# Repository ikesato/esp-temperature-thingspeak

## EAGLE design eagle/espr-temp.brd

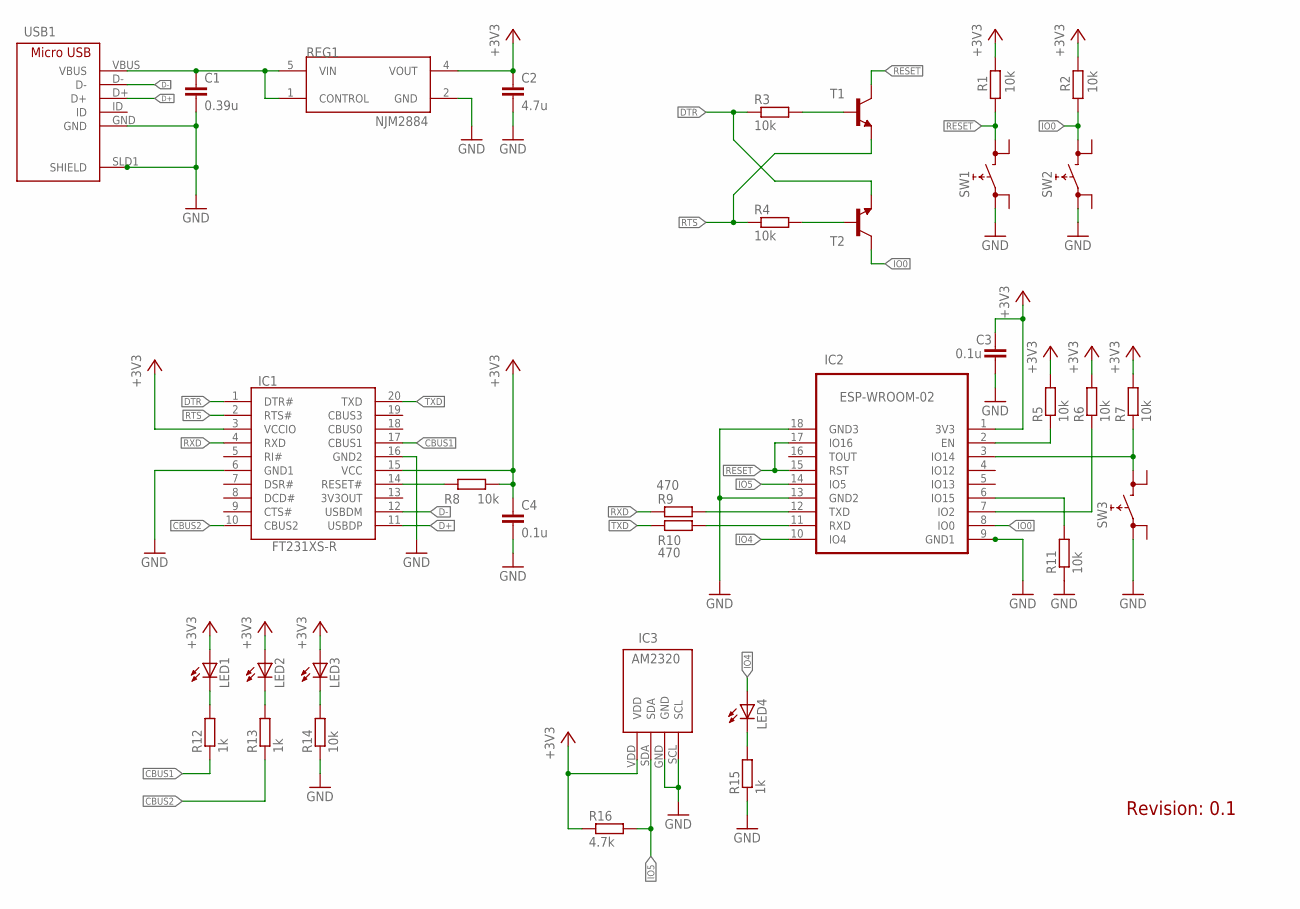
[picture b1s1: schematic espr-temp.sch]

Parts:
C1: 0.39u; C1608
C2: 4.7u; C3216
C3, C4: 0.1u; C2012
IC1: FT231XS-R; SOP64P599X175-20N
IC2: ESP-WROOM-02
IC3: AM2320
LED1: OSHR1608; C1608
LED2: OSYG1608; C1608
LED3: OSYL1608; C1608
LED4: OSBL1608; C1608
R1, R2, R3, R4, R5, R6, R7, R8, R11, R14: 10k; R1608
R9, R10: 470; R1608
R12, R13, R15: 1k; R1608
R16: 4.7k; M0805
REG1: NJM2884; NJM2884-SOT-89-5
SW1, SW2, SW3: SKRPACE010
T1, T2: 2PD601A; SOT346
USB1: MICRO-USB; ZX62B5PA

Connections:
+3V3: C2.1, C3.1, C4.1, IC1.3 (VCCIO), IC1.15 (VCC), IC2.1 (3V3), IC3.VDD, LED1.A, LED2.A, LED3.A, R1.2, R2.2, R5.2, R6.2, R7.2, R8.2, R16.1, REG1.4 (VOUT)
CBUS1: IC1.17 (CBUS1), R12.1
CBUS2: IC1.10 (CBUS2), R13.1
D+: IC1.11 (USBDP), USB1.D+
D-: IC1.12 (USBDM), USB1.D-
DTR: IC1.1 (DTR#), R3.1, T2.2 (E)
GND: C1.2, C2.2, C3.2, C4.2, IC1.6 (GND1), IC1.16 (GND2), IC2.9 (GND1), IC2.13 (GND2), IC2.18 (GND3), IC2.19 (GND0), IC3.GND, IC3.SCL, R11.1, R14.1, R15.1, REG1.2 (GND), SW1.1 (0), SW2.1 (0), SW3.1 (0), USB1.GND, USB1.SLD1 (SHIELD), USB1.SLD2 (SHIELD2), USB1.SLD3 (SHIELD3), USB1.SLD4 (SHIELD4), USB1.SLD5 (SHIELD5), USB1.SLD6 (SHIELD6)
IO0: IC2.8 (IO0), R2.1, SW2.3 (1), T2.3 (C)
IO4: IC2.10 (IO4), LED4.A
IO5: IC2.14 (IO5), IC3.SDA, R16.2
unnamed: IC2.2 (EN), R5.1
unnamed: LED4.C, R15.2
unnamed: IC2.7 (IO2), R6.1
unnamed: C1.1, REG1.1 (CONTROL), REG1.5 (VIN), USB1.VBUS
unnamed: LED1.C, R12.2
unnamed: R3.2, T1.1 (B)
unnamed: R4.2, T2.1 (B)
unnamed: LED2.C, R13.2
unnamed: LED3.C, R14.2
unnamed: IC2.12 (TXD), R9.2
unnamed: IC2.11 (RXD), R10.2
unnamed: IC2.6 (IO15), R11.2
unnamed: IC1.14 (RESET#), R8.1
unnamed: IC2.3 (IO14), R7.1, SW3.3 (1)
RESET: IC2.15 (RST), IC2.17 (IO16), R1.1, SW1.3 (1), T1.3 (C)
RTS: IC1.2 (RTS#), R4.1, T1.2 (E)
RXD: IC1.4 (RXD), R9.1
TXD: IC1.20 (TXD), R10.1

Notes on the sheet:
Revision: 0.1

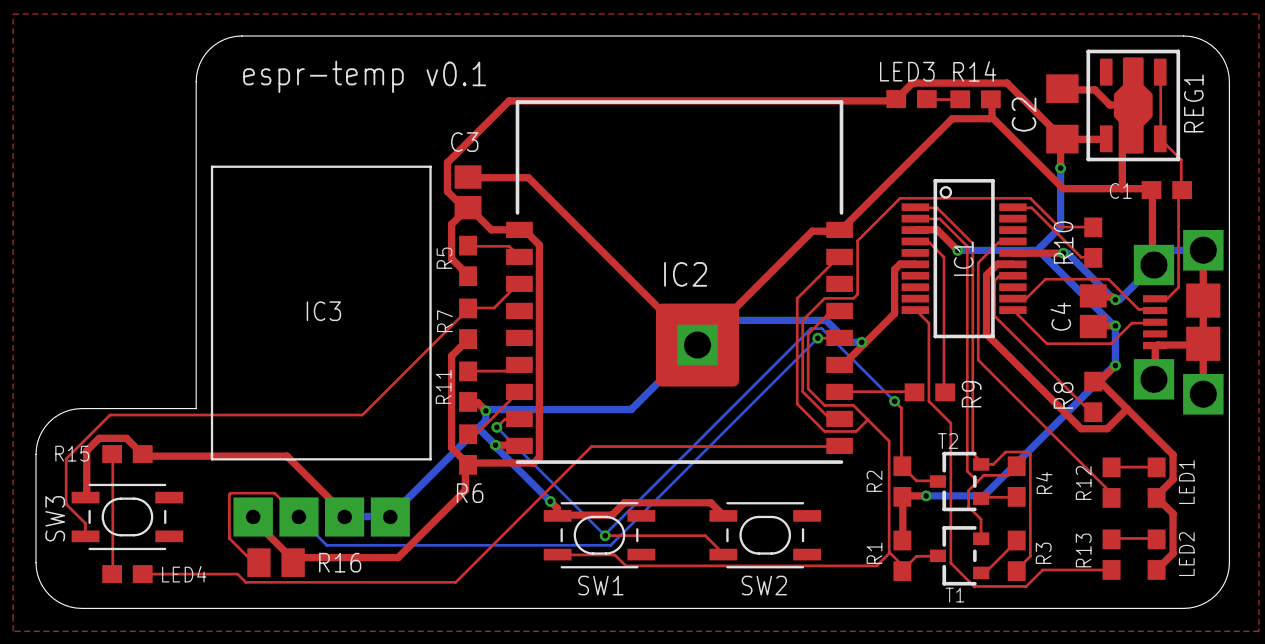
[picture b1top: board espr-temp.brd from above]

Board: 2 copper layers, 66.3 x 31.8 mm, 34 parts (0 on the bottom side), 28 nets.

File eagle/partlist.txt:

Partlist

Exported from espr-temp.sch at 2018/05/29 20:20

EAGLE Version 8.3.1 Copyright (c) 1988-2017 Autodesk, Inc.

Assembly variant: 

Part     Value          Device                 Package           Library       Sheet   value? akituki? have?

C1       0.39u          C-EUC1608              C1608             rcl           1       x      x        仙石で買う
C2       4.7u           C-EUC3216              C3216             rcl           1       x      x        x
C3       0.1u           C-EUC2012              C2012             rcl           1       x      x        x
C4       0.1u           C-EUC2012              C2012             rcl           1       x      x        x
IC1      FT231XS-R      FT231XS-R              SOP64P599X175-20N FT231XS-R     1       x      x        x
IC2      ESP-WROOM-02   ESP-WROOM-02FRONT-FACE FRONT-FACE        esp-wroom-02  1       x      x        x
IC3      AM2320         AM2320                 AM2320            am2320        1       x      x        x
LED1     (RX red)       OSHR1608               C1608             led-smd       1       x      x        秋月で買う
LED2     (TX green)     OSYG1608               C1608             led-smd       1       x      x        x
LED3     (prw yellow)   OSYL1608               C1608             led-smd       1       x      x        x
LED4     (apl blue)     OSBL1608               C1608             led-smd       1       x      x        秋月で買う
R1       10k            R1608                  R1608             registors     1       x      x        仙石0.1w 1608 を買う
R2       10k            R1608                  R1608             registors     1       x      x        仙石0.1w 1608 を買う
R3       10k            R1608                  R1608             registors     1       x      x        仙石0.1w 1608 を買う
R4       10k            R1608                  R1608             registors     1       x      x        仙石0.1w 1608 を買う
R5       10k            R1608                  R1608             registors     1       x      x        仙石0.1w 1608 を買う
R6       10k            R1608                  R1608             registors     1       x      x        仙石0.1w 1608 を買う
R7       10k            R1608                  R1608             registors     1       x      x        仙石0.1w 1608 を買う
R8       10k            R1608                  R1608             registors     1       x      x        仙石0.1w 1608 を買う
R9       470            R1608                  R1608             registors     1       x      x        仙石0.1w 1608 を買う
R10      470            R1608                  R1608             registors     1       x      x        仙石0.1w 1608 を買う
R11      10k            R1608                  R1608             registors     1       x      x        仙石0.1w 1608 を買う
R12      1k             R1608                  R1608             registors     1       x      x        仙石0.1w 1608 を買う
R13      1k             R1608                  R1608             registors     1       x      x        仙石0.1w 1608 を買う
R14      10k            R1608                  R1608             registors     1       x      x        仙石0.1w 1608 を買う
R15      1k             R1608                  R1608             registors     1       x      x        仙石0.1w 1608 を買う
R16      4.7k           R-EU_M0805             M0805             rcl           1       x      x        x TODO:ほんとに持ってる？
REG1     NJM2884U1      NJM2884U1              SOT-89-5          regulator     1       x      x        秋月で買う
SW1                     SKRPACE010             SKRPACE010        switches      1       x      x        x
SW2                     SKRPACE010             SKRPACE010        switches      1       x      x        x
SW3                     SKRPACE010             SKRPACE010        switches      1       x      x        x
T1                      2PD601A                SOT346            transistors   1       x      x        秋月で買う
T2                      2PD601A                SOT346            transistors   1       x      x        秋月で買う
USB1     MICRO-USB      MICRO-USB              ZX62B5PA          usb-connector 1       x      x        x

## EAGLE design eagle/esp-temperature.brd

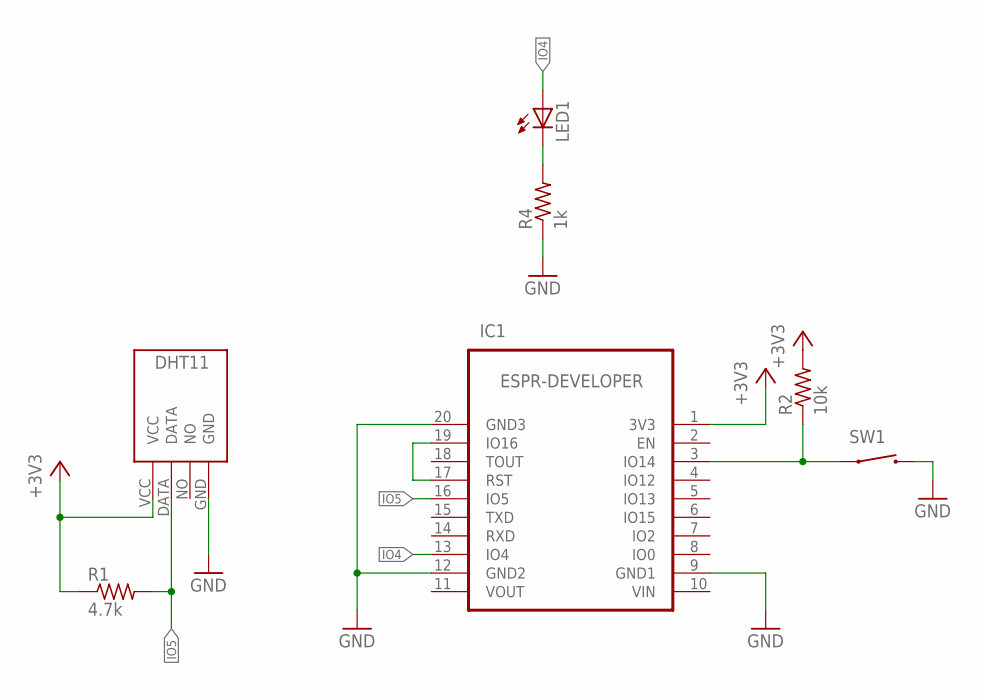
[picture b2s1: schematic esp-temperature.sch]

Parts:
IC1: ESPR-DEVELOPER
LED1: LED-SIDEUP2; LED5MM-SIDE-UP2
R1: 4.7k; R0805
R2: 10k; R0805
R4: 1k; R0805
SW1: TVBP06
U$1: DHT11

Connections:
+3V3: IC1.1 (3V3), R1.1, R2.2, U$1.VCC
GND: IC1.9 (GND1), IC1.12 (GND2), IC1.20 (GND3), R4.1, SW1.2, U$1.GND
IO4: IC1.13 (IO4), LED1.A
IO5: IC1.16 (IO5), R1.2, U$1.DATA
unnamed: IC1.3 (IO14), R2.1, SW1.1
unnamed: LED1.K (C), R4.2
unnamed: IC1.17 (RST), IC1.19 (IO16)
VIN: IC1.10 (VIN)
VOUT: IC1.11 (VOUT)

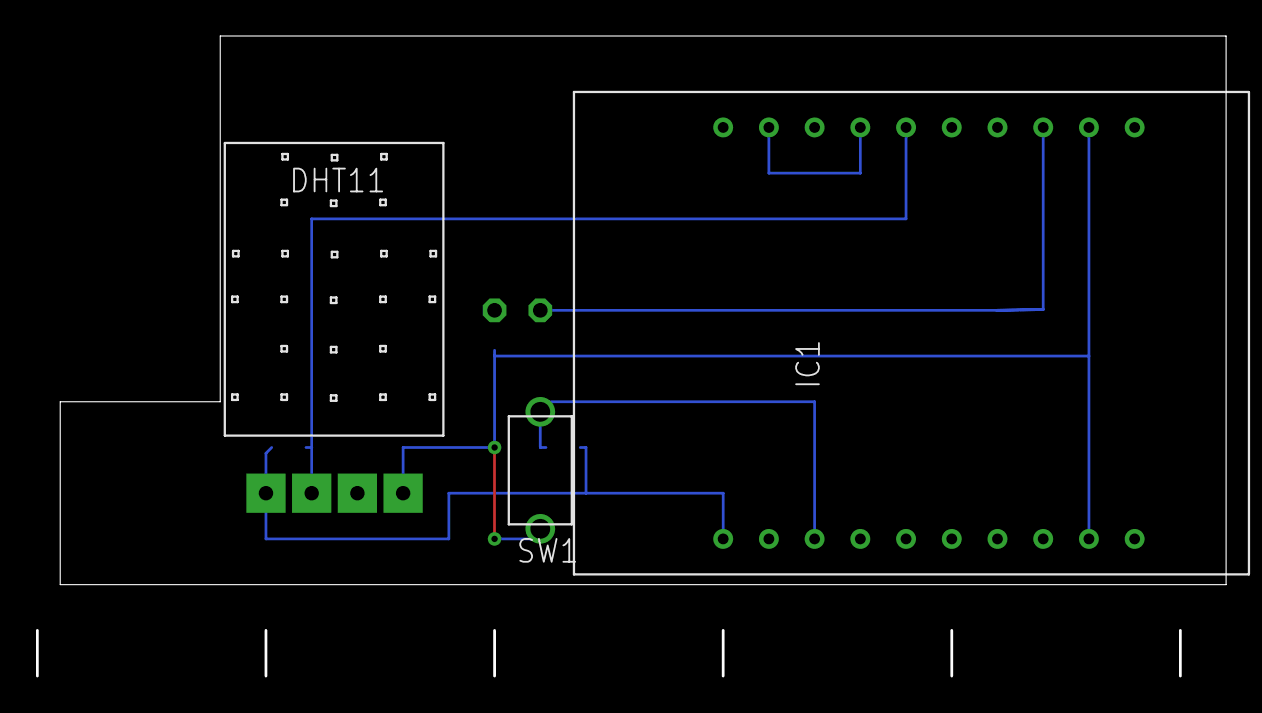
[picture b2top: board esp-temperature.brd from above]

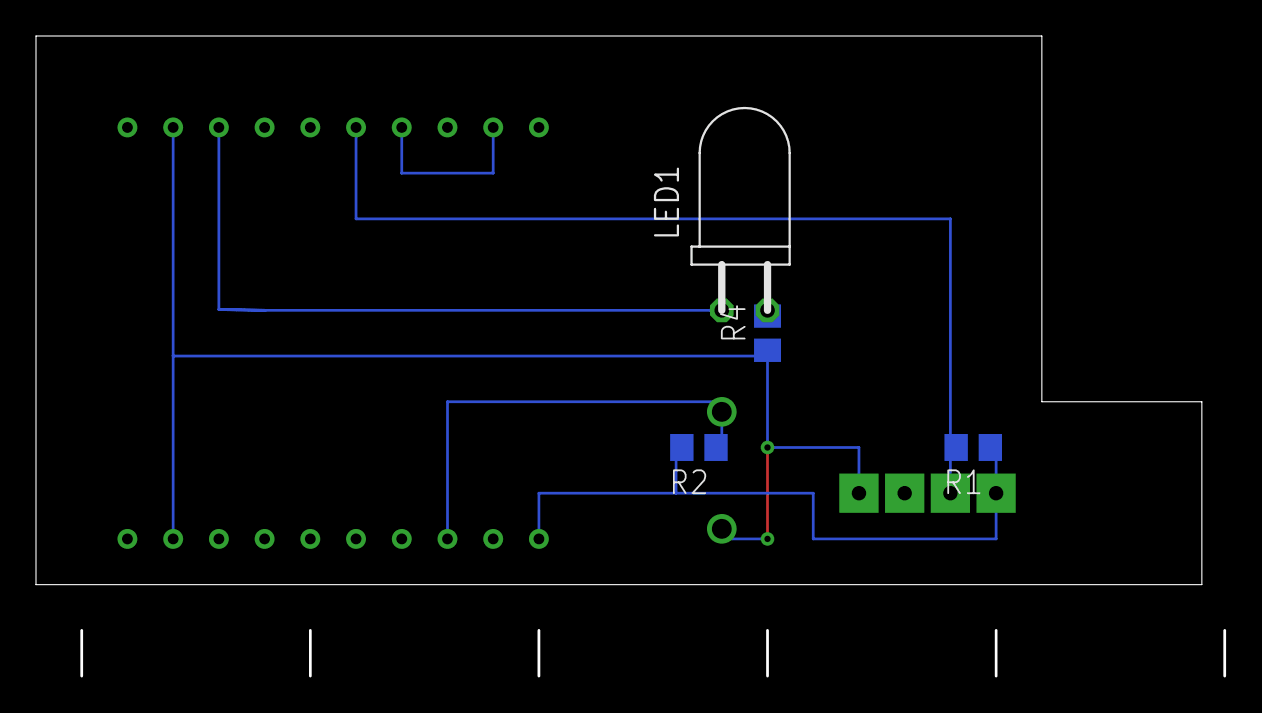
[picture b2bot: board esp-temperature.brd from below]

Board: 2 copper layers, 66.0 x 35.5 mm, 7 parts (4 on the bottom side), 7 nets.

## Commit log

2018-05-14 Add eagle files
2018-05-14 used RTC memory
2018-05-21 fix write RTC memory position
2018-05-21 add disconfort index
2018-05-21 add AM2320 sensor
2018-05-21 updated EAGLE project file
2018-05-29 add espr-temp project
2018-05-29 add gerver files for JLCPCB
2018-05-29 add zip of gerber files for JLCPCB
2018-05-29 add .gitignore
2018-05-29 remove unused files
2018-05-29 moved silk 'REG1' and made the font a little bigger
2018-05-29 add report file of AutoRouting
2018-05-29 fix some ERC errors
2018-05-30 change to GND from tRistrict for WROOM2 library
